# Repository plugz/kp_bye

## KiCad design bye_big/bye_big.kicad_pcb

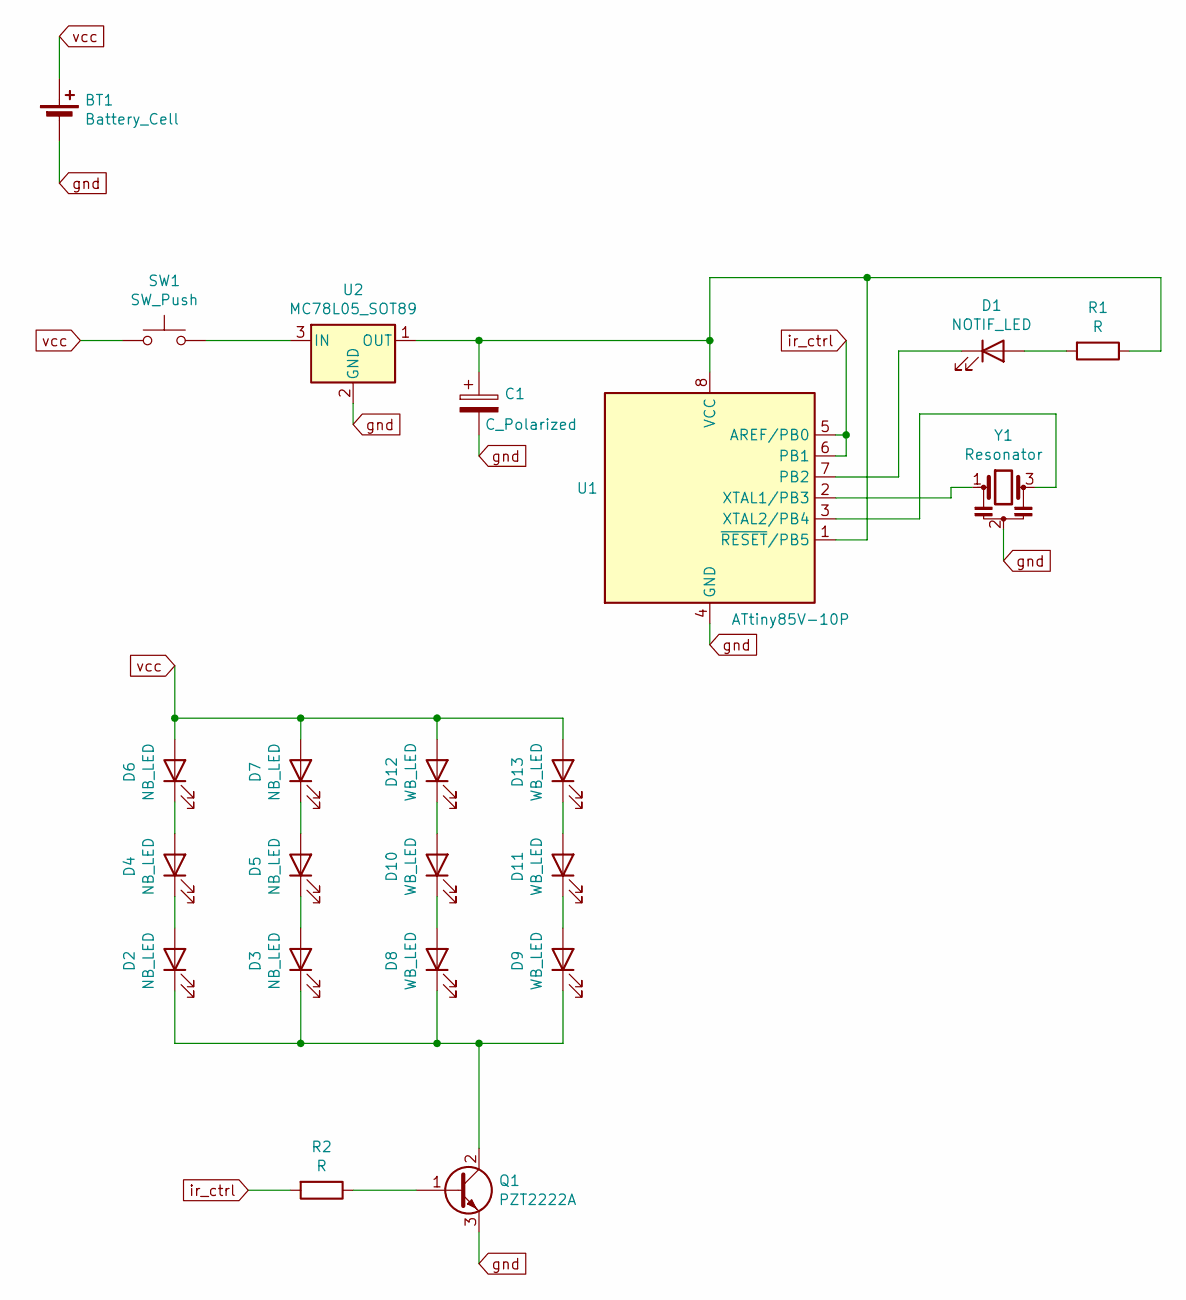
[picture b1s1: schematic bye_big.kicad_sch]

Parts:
BT1: Battery_Cell; BatteryHolder_Eagle_12BH611-GR_REMOVE_ONE_HOLE
C1: C_Polarized; CP_Elec_6.3x5.4
D1: NOTIF_LED; LED_D3.0mm_Horizontal_O1.27mm_Z2.0mm
D2, D3, D4, D5, D6, D7: NB_LED; LED_D5.0mm_IRBlack
D8, D9, D10, D11, D12, D13: WB_LED; LED_D5.0mm_IRGrey
Q1: PZT2222A; SOT-223
R1, R2: R; R_1206_3216Metric
SW1: SW_Push; SW_Tactile_SPST_Angled_PTS645Vx58-2LFS
U1: ATtiny85V-10P; DIP-8_W7.62mm
U2: MC78L05_SOT89; SOT-89-3
Y1: Resonator; Resonator-3Pin_W8.0mm_H3.5mm

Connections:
unnamed: D1.2 (A), R1.2
unnamed: D1.1 (K), U1.7 (PB2)
unnamed: D2.2 (A), D4.1 (K)
unnamed: D2.1 (K), D3.1 (K), D8.1 (K), D9.1 (K), Q1.2 (C)
unnamed: D3.2 (A), D5.1 (K)
unnamed: D4.2 (A), D6.1 (K)
unnamed: D5.2 (A), D7.1 (K)
unnamed: D10.2 (A), D12.1 (K)
unnamed: D8.2 (A), D10.1 (K)
unnamed: D11.2 (A), D13.1 (K)
unnamed: D9.2 (A), D11.1 (K)
unnamed: Q1.1 (B), R2.1
unnamed: C1.1, R1.1, U1.1 (~RESET/PB5), U1.8 (VCC), U2.1 (OUT)
unnamed: U1.2 (XTAL1/PB3), Y1.1
unnamed: U1.3 (XTAL2/PB4), Y1.3
unnamed: SW1.2, U2.3 (IN)
gnd: BT1.2 (-), C1.2, Q1.3 (E), U1.4 (GND), U2.2 (GND), Y1.2
ir_ctrl: R2.2, U1.5 (AREF/PB0), U1.6 (PB1)
vcc: BT1.1 (+), D6.2 (A), D7.2 (A), D12.2 (A), D13.2 (A), SW1.1

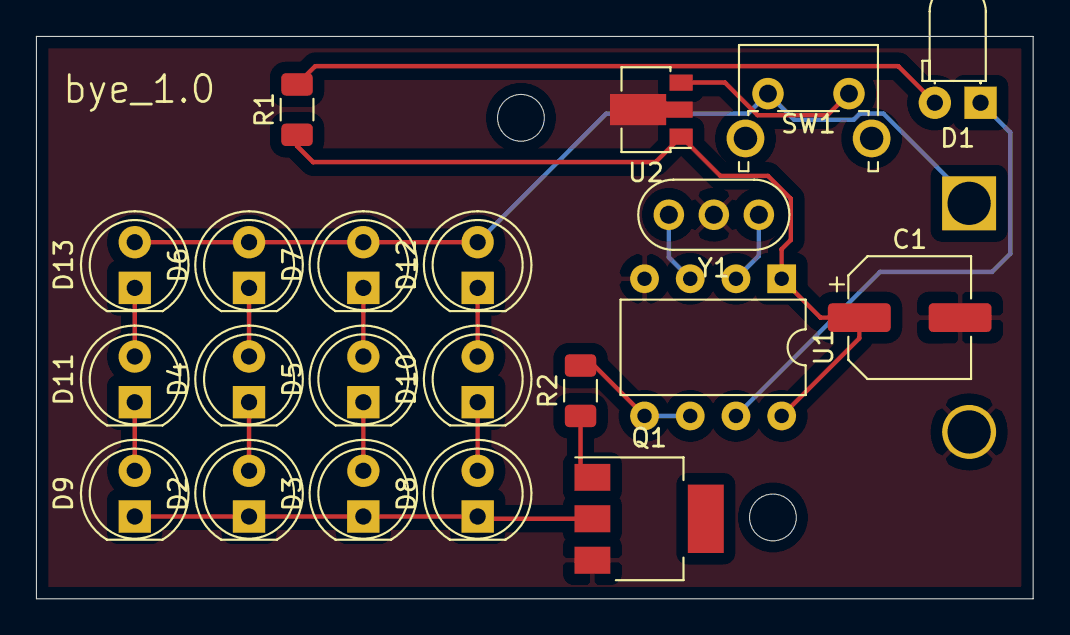
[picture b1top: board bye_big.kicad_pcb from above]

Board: 2 copper layers, 55.4 x 31.2 mm, 22 parts (1 on the bottom side), 19 nets.

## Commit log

2020-09-22 init commit
2020-09-22 add files
2020-10-02 bye_big: FIX gnd not connected on uC
2023-08-05 update to kicad 7
2023-08-05 add 7.0 files, fix missing symbols
